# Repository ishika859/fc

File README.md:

# STM32F405 Flight Controller

Custom flight controller board based on the STM32F405RGT6 ARM Cortex-M4 microcontroller.

The board is designed as a compact flight-control platform with an onboard IMU, barometric sensor, four motor outputs, USB-C connectivity, removable storage, multiple serial interfaces and battery monitoring.

This repository contains the KiCad schematic, PCB layout, manufacturing files, bill of materials, firmware starter code and project documentation.

## Why This Project?

The goal of this project was to design a complete flight controller from the schematic level instead of only using an existing development board.

The work included selecting the controller and sensors, designing the power sections, assigning footprints, placing components, routing the PCB, checking the board in KiCad and preparing the manufacturing files.

The project also provides a useful platform for learning how sensor data, motor outputs, communication ports and power monitoring work together in an embedded flight-control system.

## Hardware

| Feature | Description |
|---|---|
| **Microcontroller** | STM32F405RGT6 ARM Cortex-M4, 168 MHz, 1 MB Flash |
| **Inertial sensor** | TDK InvenSense ICM-42688-P 6-axis IMU |
| **Barometer** | Bosch BMP280 pressure sensor |
| **Motor outputs** | Four outputs for M1, M2, M3 and M4 ESC connections |
| **Battery input** | 2S to 6S battery connector with voltage sensing |
| **Current sensing** | Analog current-monitor input |
| **Power regulation** | AP63205WU buck regulator and AP2112K-3.3 LDO |
| **USB connectivity** | USB-C connector with USB ESD protection |
| **Removable storage** | microSD card connector |
| **Serial interfaces** | UART1 receiver, UART3 GPS and I2C, UART4 VTX, UART6 auxiliary port |
| **Debug interface** | 1.27 mm SWD connector |
| **User connections** | LED strip output and buzzer connector |
| **PCB** | Two-layer KiCad PCB layout |

## Main Connections

The ICM-42688-P is connected to the STM32 through SPI. The BMP280 uses the I2C bus shared with the GPS expansion connector.

The four motor nets are connected as follows:

| Motor | MCU pin |
|---|---|
| M1 | PB0 |
| M2 | PB1 |
| M3 | PA3 |
| M4 | PA2 |

The board also includes ADC inputs for battery voltage and current measurement, plus status LEDs and a buzzer driver.

## Project Images

### 3D PCB Design

The board can be inspected in KiCad's 3D Viewer to check component placement, connector access and the overall mechanical layout.

### PCB Layout and Routing

### Circuit Schematic

## Bill of Materials

The component list with purchase links and estimated prices is available in [`bom.csv`](bom.csv).

The current estimated component subtotal is approximately **$31.27 USD** before shipping and taxes. Prices are indicative and can change with supplier stock and order quantity.

Important main parts include:

| Component | Quantity | Description |
|---|---:|---|
| STM32F405RGT6 | 1 | Main flight-controller microcontroller |
| ICM-42688-P | 1 | Accelerometer and gyroscope |
| BMP280 | 1 | Barometric pressure sensor |
| AP63205WU | 1 | Buck regulator |
| AP2112K-3.3 | 1 | 3.3 V linear regulator |
| USBLC6-2SC6 | 1 | USB ESD protection device |
| USB-C receptacle | 1 | USB connection |
| microSD connector | 1 | Flight log storage interface |

## Firmware

The firmware starter is located in [`firmware/`](firmware/).

The initial firmware structure is based on the STM32F405 pin mapping from the schematic and includes the basic peripheral mapping for:

- SPI1 for the ICM-42688-P
- I2C1 for the BMP280
- Four motor output connections
- Battery and current ADC inputs
- UART1, UART3, UART4 and UART6
- USB detect, LEDs and buzzer control

The starter firmware keeps all motor outputs disabled. It is intended for bench testing and peripheral bring-up only. A complete flight firmware still requires sensor initialization, calibration, receiver protocol support, attitude estimation, PID control, motor timing, arming logic and failsafe handling.

Always test firmware with propellers removed until the motor mapping, sensor orientation and failsafe behavior have been verified.

## Repository Structure

```text
hardware/
  flight_controller.kicad_sch
  flight_controller.kicad_pcb

firmware/
  main.c
  README.md

manufacturing/
  gerbers/
  gerbers.zip

documentation/
  project journal and design notes

bom.csv
README.md
```

## Design Verification

The current PCB has been checked in KiCad and the present board revision reports no remaining DRC warnings or errors.

The schematic and PCB should still be reviewed against the final assembled components before ordering. Particular attention should be given to the USB-C shell pads, connector mounting pads, regulator layout, sensor orientation and the motor-output order.

## Manufacturing

The `manufacturing/gerbers/` folder contains the exported Gerber and drill files needed to order the PCB.

The manufacturing package includes:

- Front and back copper
- Front and back solder mask
- Front and back silkscreen
- Paste layers where required
- Edge cuts board outline
- Plated and non-plated drill files
- Gerber job file

Before ordering, upload the Gerber archive to the chosen PCB manufacturer and confirm that the board outline, layer count, drill files and solder-mask openings are detected correctly.

## Project Status

The hardware design, schematic, PCB layout, BOM and manufacturing outputs are complete for the current revision.

The next stage is hardware bring-up. This includes checking the power rails, programming through SWD, confirming USB communication, reading the IMU and barometer, testing the ADC inputs and validating each motor output independently.

## License

Add the project license here before publishing the repository.

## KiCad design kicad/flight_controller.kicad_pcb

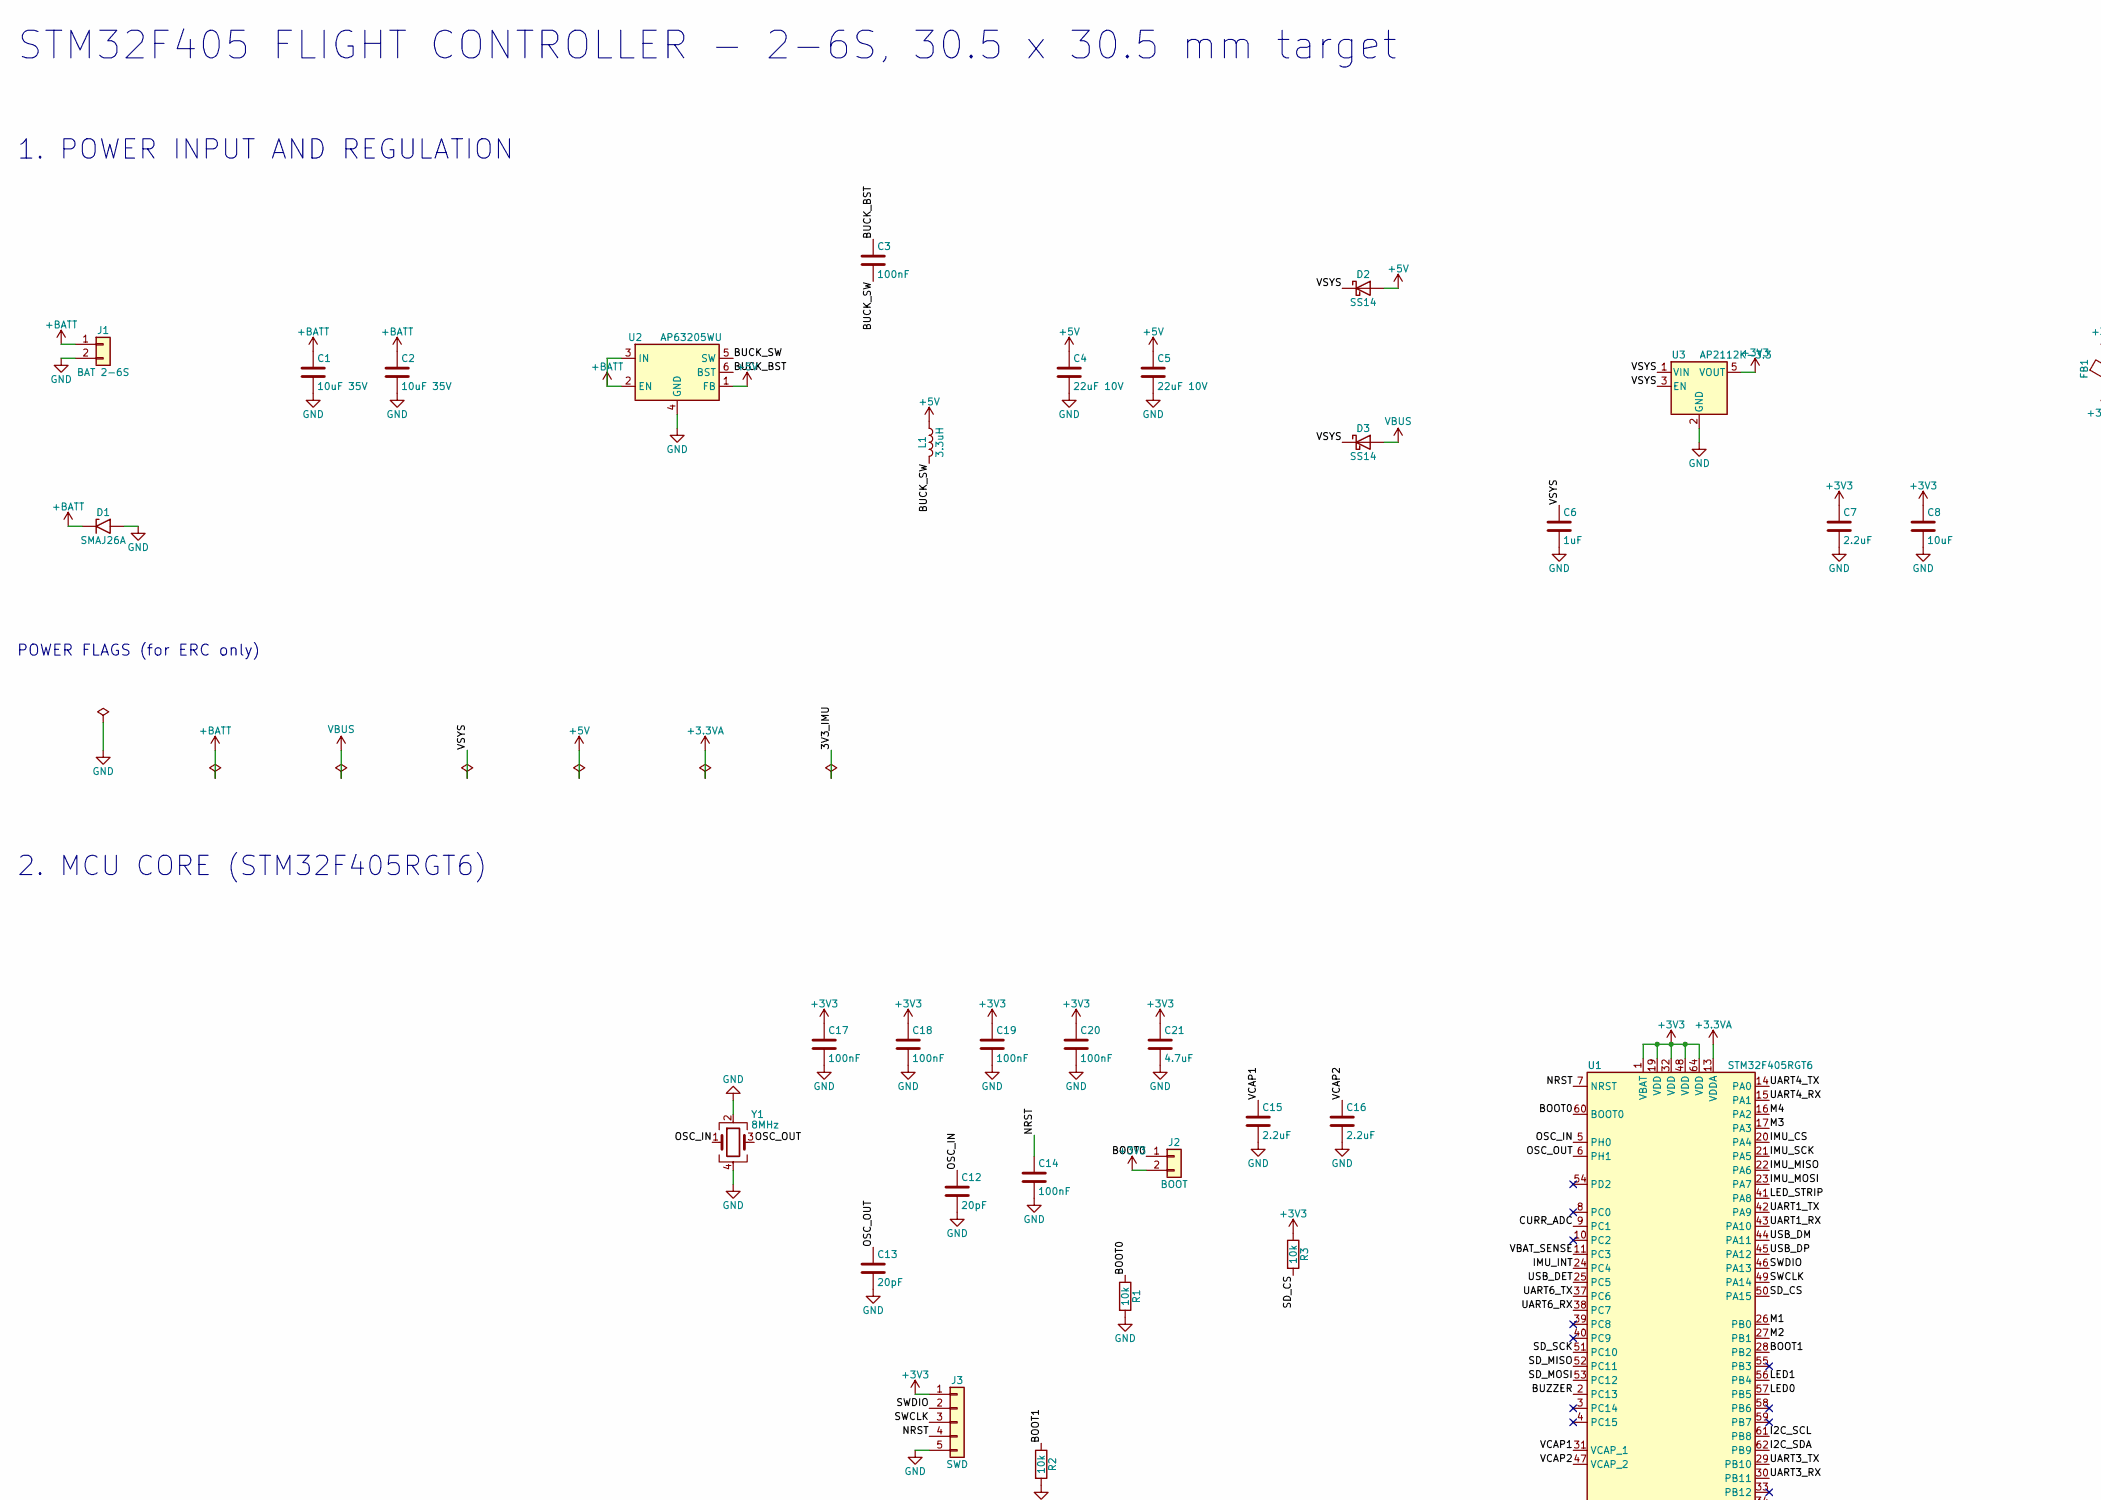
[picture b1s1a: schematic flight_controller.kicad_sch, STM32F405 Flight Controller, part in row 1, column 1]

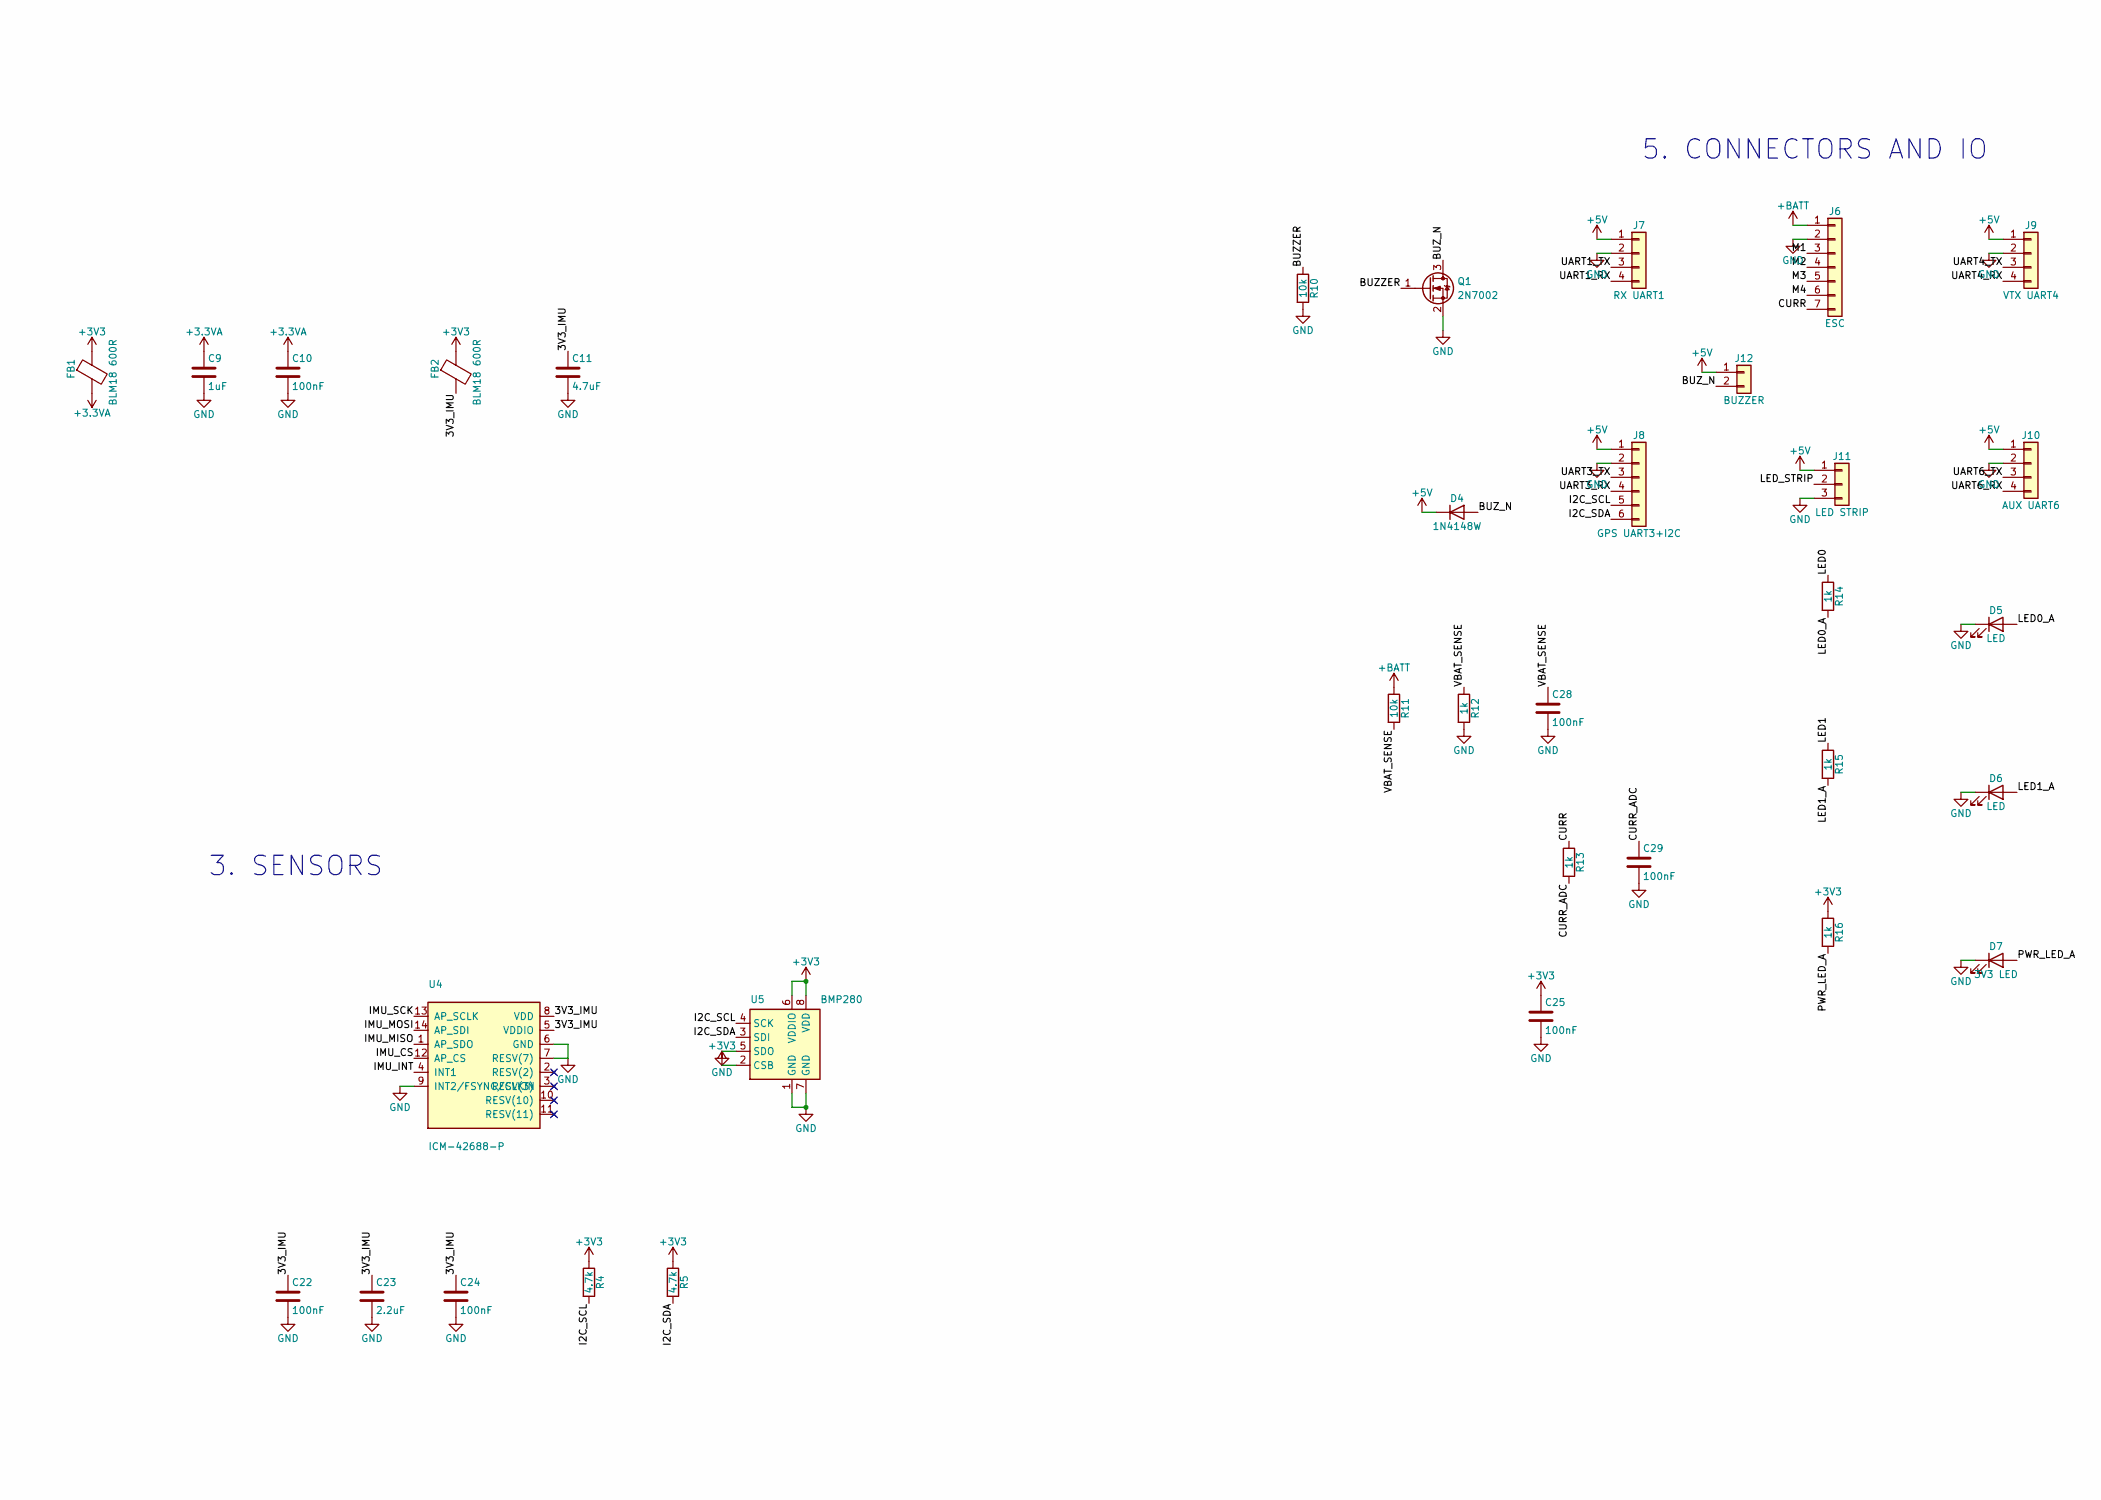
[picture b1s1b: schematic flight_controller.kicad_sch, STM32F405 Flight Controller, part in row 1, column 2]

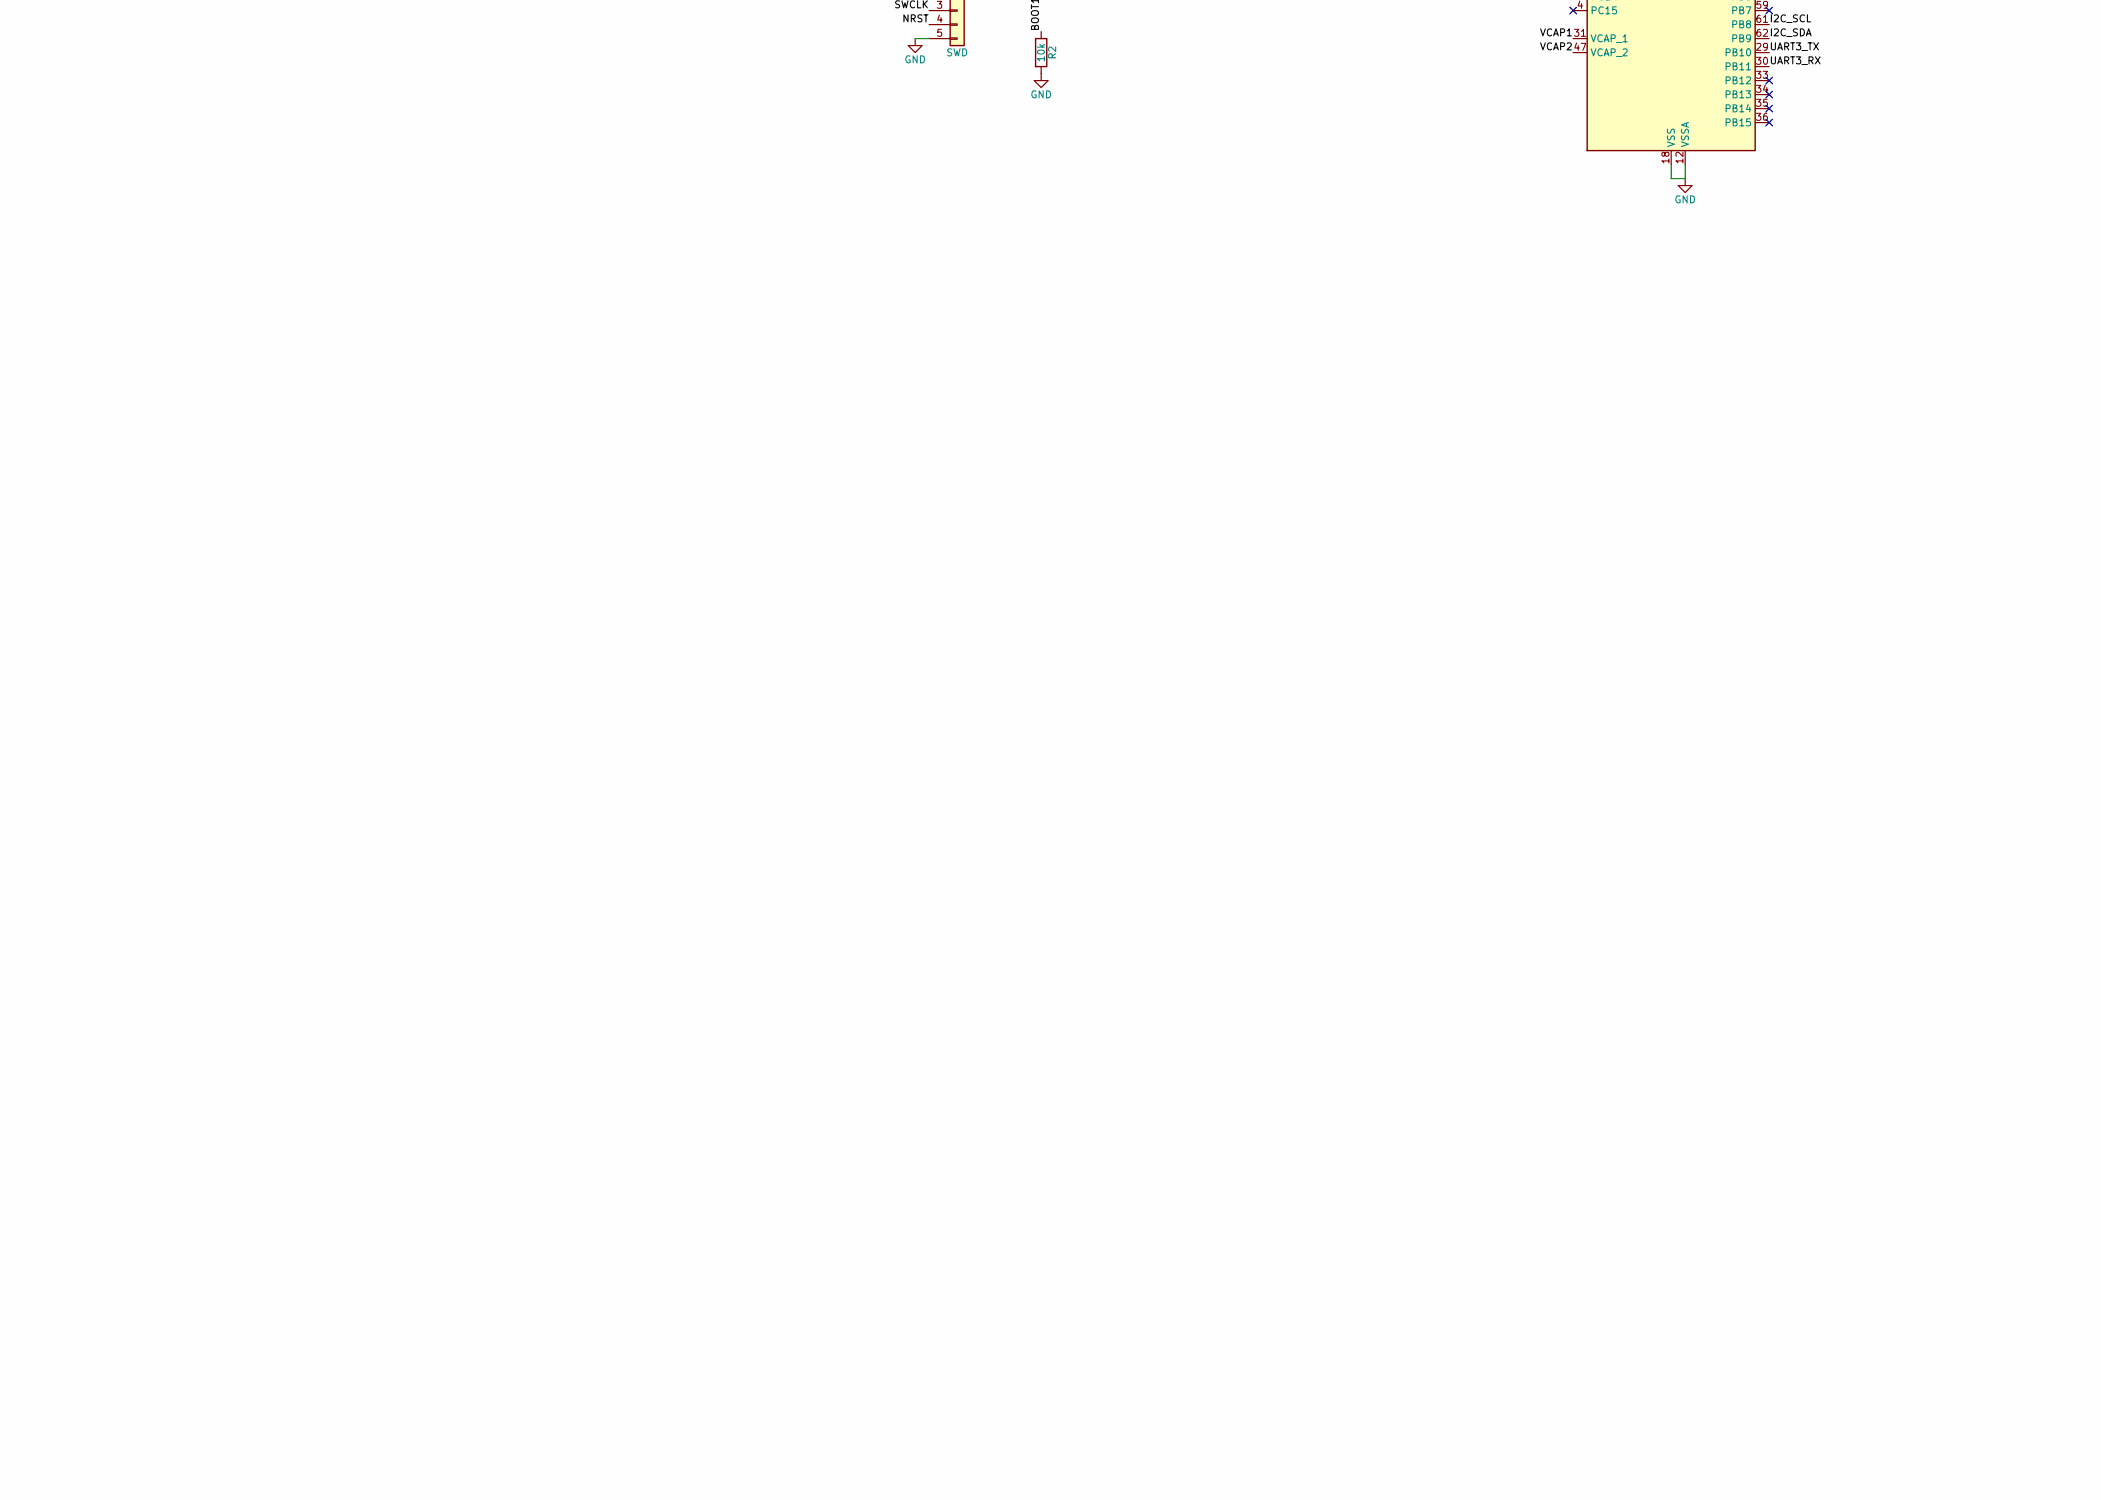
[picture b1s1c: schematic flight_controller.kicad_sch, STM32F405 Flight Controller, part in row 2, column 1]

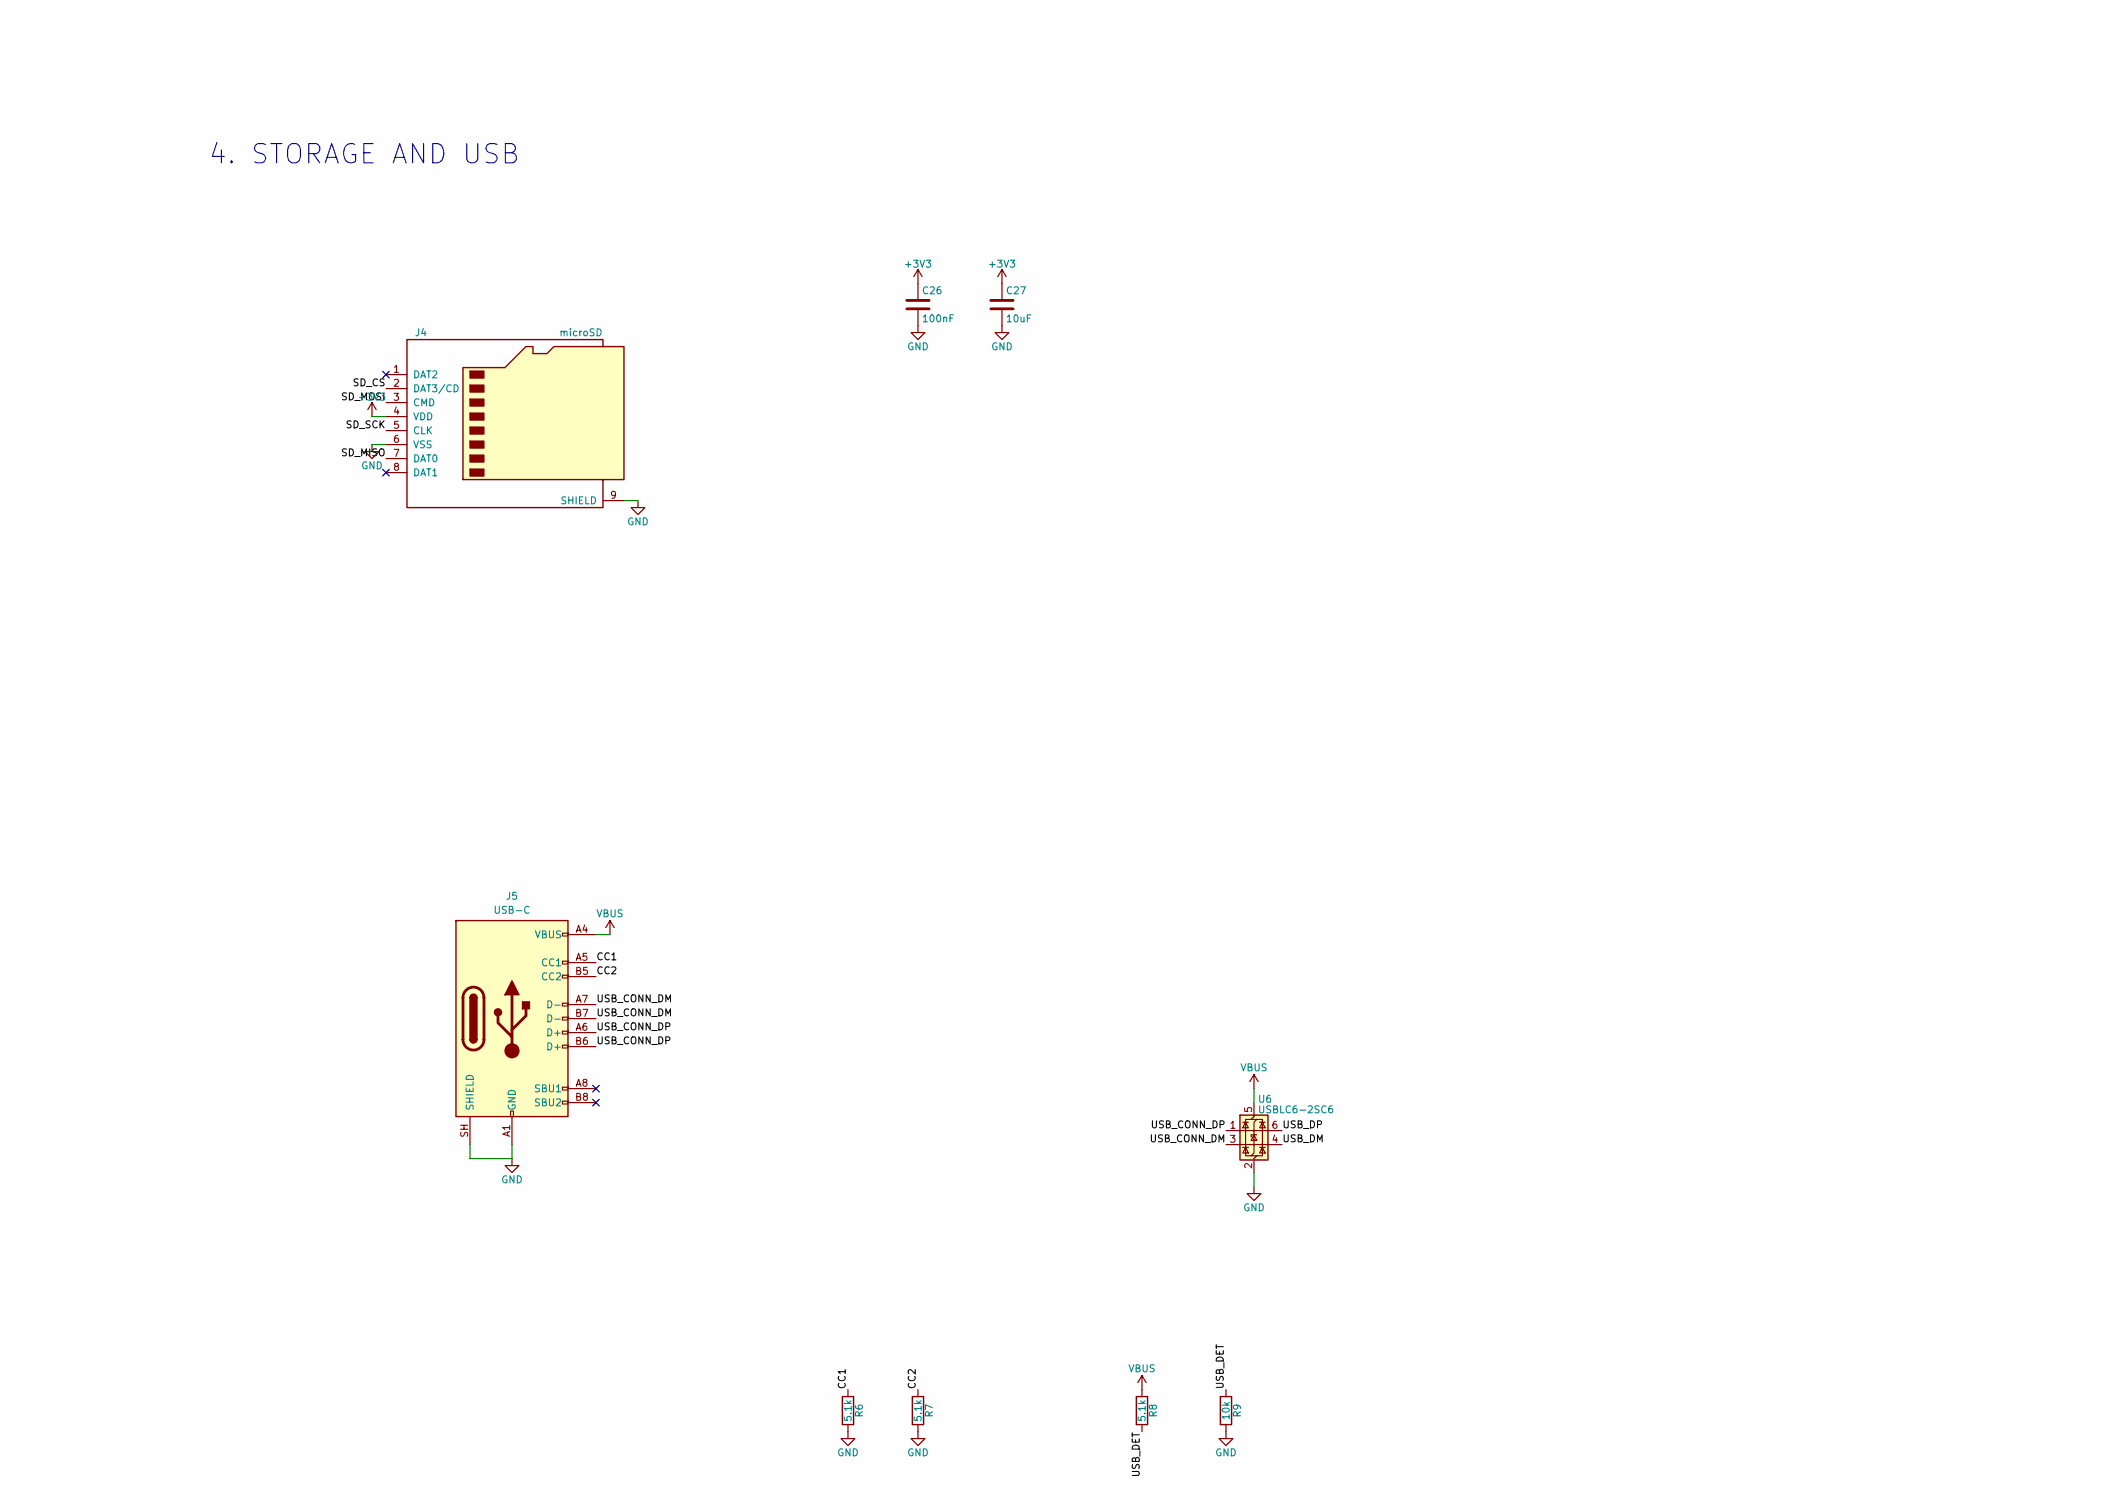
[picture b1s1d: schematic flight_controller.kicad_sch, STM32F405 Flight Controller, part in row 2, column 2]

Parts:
C1, C2: 10uF 35V; C_1206_3216Metric
C3, C10, C14, C17, C18, C19, C20, C22, C24, C25, C26, C28, C29: 100nF; C_0402_1005Metric
C4, C5: 22uF 10V; C_0805_2012Metric
C6, C9: 1uF; C_0402_1005Metric
C7, C15, C16, C23: 2.2uF; C_0402_1005Metric
C8, C27: 10uF; C_0805_2012Metric
C11, C21: 4.7uF; C_0805_2012Metric
C12, C13: 20pF; C_0402_1005Metric
D1: SMAJ26A; D_SMA
D2, D3: SS14; D_SMA
D4: 1N4148W; D_SOD-123
D5, D6: LED; LED_0603_1608Metric
D7: 3V3 LED; LED_0603_1608Metric
FB1, FB2: BLM18 600R; L_0603_1608Metric
J1: BAT 2-6S; PinHeader_1x02_P2.54mm_Vertical
J2: BOOT; PinHeader_1x02_P1.27mm_Vertical
J3: SWD; PinHeader_1x05_P1.27mm_Vertical
J4: microSD; microSD_HC_Hirose_DM3AT-SF-PEJM5
J5: USB-C; USB_C_Receptacle_HRO_TYPE-C-31-M-12
J6: ESC; PinHeader_1x07_P1.00mm_Vertical
J7: RX UART1; JST_SH_SM04B-SRSS-TB_1x04-1MP_P1.00mm_Horizontal
J8: GPS UART3+I2C; JST_SH_SM06B-SRSS-TB_1x06-1MP_P1.00mm_Horizontal
J9: VTX UART4; JST_SH_SM04B-SRSS-TB_1x04-1MP_P1.00mm_Horizontal
J10: AUX UART6; JST_SH_SM04B-SRSS-TB_1x04-1MP_P1.00mm_Horizontal
J11: LED STRIP; JST_SH_SM03B-SRSS-TB_1x03-1MP_P1.00mm_Horizontal
J12: BUZZER; PinHeader_1x02_P1.27mm_Vertical
L1: 3.3uH; L_Taiyo-Yuden_NR-50xx
Q1: 2N7002; SOT-23
R1, R2, R3, R9, R10, R11: 10k; R_0402_1005Metric
R4, R5: 4.7k; R_0402_1005Metric
R6, R7, R8: 5.1k; R_0402_1005Metric
R12, R13, R14, R15, R16: 1k; R_0402_1005Metric
U1: STM32F405RGT6; LQFP-64_10x10mm_P0.5mm
U2: AP63205WU; TSOT-23-6
U3: AP2112K-3.3; SOT-23-5
U4: ICM-42688-P; LGA-14_3x2.5mm_P0.5mm_LayoutBorder3x4y
U5: BMP280; Bosch_LGA-8_2x2.5mm_P0.65mm_ClockwisePinNumbering
U6: USBLC6-2SC6; SOT-23-6
Y1: 8MHz; Crystal_SMD_3225-4Pin_3.2x2.5mm

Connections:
+3.3VA: C9.1, C10.1, FB1.2, U1.13 (VDDA)
+3V3: C7.1, C8.1, C17.1, C18.1, C19.1, C20.1, C21.1, C25.1, C26.1, C27.1, FB1.1, FB2.1, J2.2, J3.1, J4.4 (VDD), R3.1, R4.1, R5.1, R16.1, U1.1 (VBAT), U1.19 (VDD), U1.32 (VDD), U1.48 (VDD), U1.64 (VDD), U3.5 (VOUT), U5.2 (CSB), U5.6 (VDDIO), U5.8 (VDD)
+5V: C4.1, C5.1, D2.2 (A), D4.1 (K), J7.1, J8.1, J9.1, J10.1, J11.1, J12.1, L1.1, U2.1 (FB)
+BATT: C1.1, C2.1, D1.1 (A1), J1.1, J6.1, R11.1, U2.2 (EN), U2.3 (IN)
/3V3_IMU: C11.1, C22.1, C23.1, C24.1, FB2.2, U4.5 (VDDIO), U4.8 (VDD)
/BOOT0: J2.1, R1.1, U1.60 (BOOT0)
/BOOT1: R2.1, U1.28 (PB2)
/BUCK_BST: C3.1, U2.6 (BST)
/BUCK_SW: C3.2, L1.2, U2.5 (SW)
/BUZZER: Q1.1 (G), R10.1, U1.2 (PC13)
/BUZ_N: D4.2 (A), J12.2, Q1.3 (D)
/CC1: J5.A5 (CC1), R6.1
/CC2: J5.B5 (CC2), R7.1
/CURR: J6.7, R13.1
/CURR_ADC: C29.1, R13.2, U1.9 (PC1)
/I2C_SCL: J8.5, R4.2, U1.61 (PB8), U5.4 (SCK)
/I2C_SDA: J8.6, R5.2, U1.62 (PB9), U5.3 (SDI)
/IMU_CS: U1.20 (PA4), U4.12 (AP_CS)
/IMU_INT: U1.24 (PC4), U4.4 (INT1)
/IMU_MISO: U1.22 (PA6), U4.1 (AP_SDO)
/IMU_MOSI: U1.23 (PA7), U4.14 (AP_SDI)
/IMU_SCK: U1.21 (PA5), U4.13 (AP_SCLK)
/LED0: R14.1, U1.57 (PB5)
/LED0_A: D5.2 (A), R14.2
/LED1: R15.1, U1.56 (PB4)
/LED1_A: D6.2 (A), R15.2
/LED_STRIP: J11.2, U1.41 (PA8)
/M1: J6.3, U1.26 (PB0)
/M2: J6.4, U1.27 (PB1)
/M3: J6.5, U1.17 (PA3)
/M4: J6.6, U1.16 (PA2)
/NRST: C14.1, J3.4, U1.7 (NRST)
/OSC_IN: C12.1, U1.5 (PH0), Y1.1
/OSC_OUT: C13.1, U1.6 (PH1), Y1.3
/PWR_LED_A: D7.2 (A), R16.2
/SD_CS: J4.2 (DAT3/CD), R3.2, U1.50 (PA15)
/SD_MISO: J4.7 (DAT0), U1.52 (PC11)
/SD_MOSI: J4.3 (CMD), U1.53 (PC12)
/SD_SCK: J4.5 (CLK), U1.51 (PC10)
/SWCLK: J3.3, U1.49 (PA14)
/SWDIO: J3.2, U1.46 (PA13)
/UART1_RX: J7.4, U1.43 (PA10)
/UART1_TX: J7.3, U1.42 (PA9)
/UART3_RX: J8.4, U1.30 (PB11)
/UART3_TX: J8.3, U1.29 (PB10)
/UART4_RX: J9.4, U1.15 (PA1)
/UART4_TX: J9.3, U1.14 (PA0)
/UART6_RX: J10.4, U1.38 (PC7)
/UART6_TX: J10.3, U1.37 (PC6)
/USB_CONN_DM: J5.A7 (D-), J5.B7 (D-), U6.3 (I/O2)
/USB_CONN_DP: J5.A6 (D+), J5.B6 (D+), U6.1 (I/O1)
/USB_DET: R8.2, R9.1, U1.25 (PC5)
/USB_DM: U1.44 (PA11), U6.4 (I/O2)
/USB_DP: U1.45 (PA12), U6.6 (I/O1)
/VBAT_SENSE: C28.1, R11.2, R12.1, U1.11 (PC3)
/VCAP1: C15.1, U1.31 (VCAP_1)
/VCAP2: C16.1, U1.47 (VCAP_2)
/VSYS: C6.1, D2.1 (K), D3.1 (K), U3.1 (VIN), U3.3 (EN)
GND: C1.2, C2.2, C4.2, C5.2, C6.2, C7.2, C8.2, C9.2, C10.2, C11.2, C12.2, C13.2, C14.2, C15.2, C16.2, C17.2, C18.2, C19.2, C20.2, C21.2, C22.2, C23.2, C24.2, C25.2, C26.2, C27.2, C28.2, C29.2, D1.2 (A2), D5.1 (K), D6.1 (K), D7.1 (K), J1.2, J3.5, J4.6 (VSS), J4.9 (SHIELD), J5.A1 (GND), J5.A12 (GND), J5.B1 (GND), J5.B12 (GND), J5.SH (SHIELD), J6.2, J7.2, J8.2, J9.2, J10.2, J11.3, Q1.2 (S), R1.2, R2.2, R6.2, R7.2, R9.2, R10.2, R12.2, U1.12 (VSSA), U1.18 (VSS), U1.63 (VSS), U2.4 (GND), U3.2 (GND), U4.6 (GND), U4.7 (RESV(7)), U4.9 (INT2/FSYNC/CLKIN), U5.1 (GND), U5.5 (SDO), U5.7 (GND), U6.2 (GND), Y1.2, Y1.4
VBUS: D3.2 (A), J5.A4 (VBUS), J5.A9 (VBUS), J5.B4 (VBUS), J5.B9 (VBUS), R8.1, U6.5 (VBUS)

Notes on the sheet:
1. POWER INPUT AND REGULATION
5. CONNECTORS AND IO
4. STORAGE AND USB
3. SENSORS
2. MCU CORE (STM32F405RGT6)
POWER FLAGS (for ERC only)
STM32F405 FLIGHT CONTROLLER - 2-6S, 30.5 x 30.5 mm target

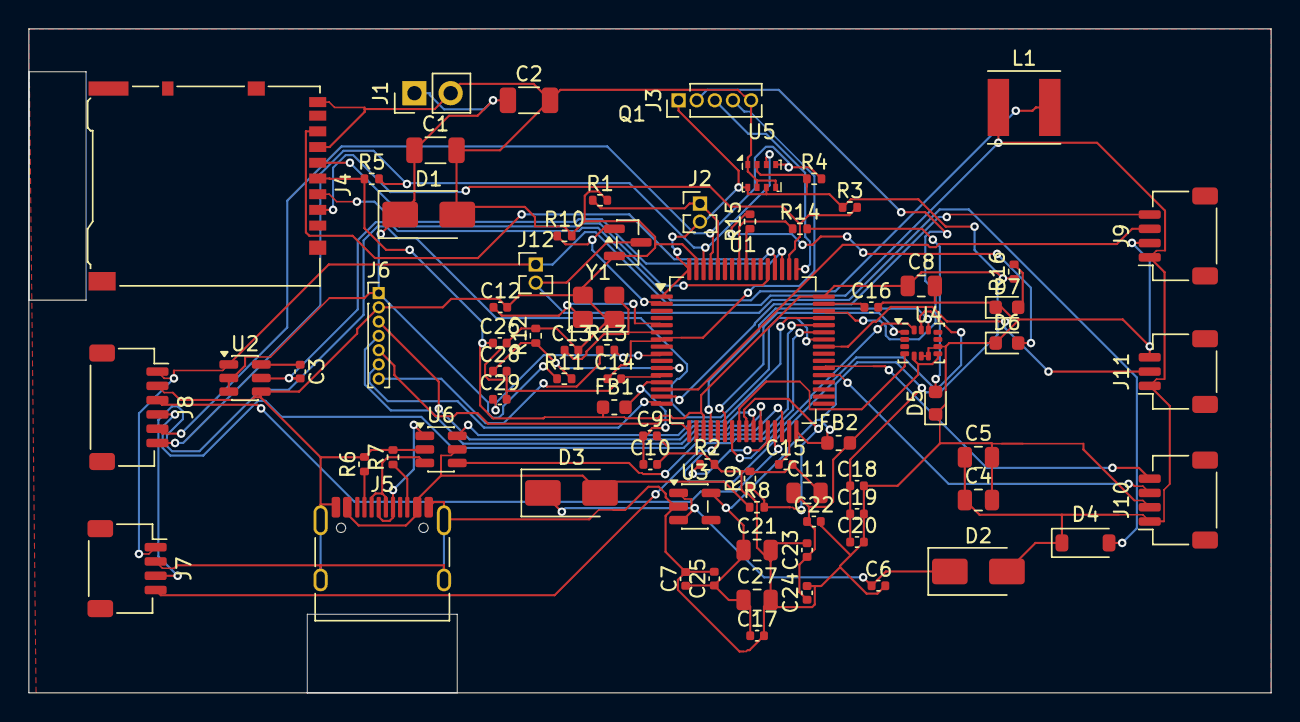
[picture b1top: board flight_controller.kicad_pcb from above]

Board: 2 copper layers, 87.0 x 46.5 mm, 75 parts (0 on the bottom side), 60 nets.

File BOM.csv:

"Id";"Designator";"Footprint";"Quantity";"Designation";"Supplier and ref";
1;"C1, C2";"C_1206_3216Metric";2;"10uF 35V";;;
2;"C3, C10, C14, C17, C18, C19, C20, C22, C24, C25, C26, C28, C29";"C_0402_1005Metric";13;"100nF";;;
3;"C4, C5";"C_0805_2012Metric";2;"22uF 10V";;;
4;"C6, C9";"C_0402_1005Metric";2;"1uF";;;
5;"C7, C15, C16, C23";"C_0402_1005Metric";4;"2.2uF";;;
6;"C8, C27";"C_0805_2012Metric";2;"10uF";;;
7;"C11, C21";"C_0805_2012Metric";2;"4.7uF";;;
8;"C12, C13";"C_0402_1005Metric";2;"20pF";;;
9;"D1";"D_SMA";1;"SMAJ26A";;;
10;"D2, D3";"D_SMA";2;"SS14";;;
11;"D4";"D_SOD-123";1;"1N4148W";;;
12;"D5, D6";"LED_0603_1608Metric";2;"LED";;;
13;"D7";"LED_0603_1608Metric";1;"3V3 LED";;;
14;"FB1, FB2";"L_0603_1608Metric";2;"BLM18 600R";;;
15;"J1";"PinHeader_1x02_P2.54mm_Vertical";1;"BAT 2-6S";;;
16;"J2";"PinHeader_1x02_P1.27mm_Vertical";1;"BOOT";;;
17;"J3";"PinHeader_1x05_P1.27mm_Vertical";1;"SWD";;;
18;"J4";"microSD_HC_Hirose_DM3AT-SF-PEJM5";1;"microSD";;;
19;"J5";"USB_C_Receptacle_HRO_TYPE-C-31-M-12";1;"USB-C";;;
20;"J6";"PinHeader_1x07_P1.00mm_Vertical";1;"ESC";;;
21;"J7";"JST_SH_SM04B-SRSS-TB_1x04-1MP_P1.00mm_Horizontal";1;"RX UART1";;;
22;"J8";"JST_SH_SM06B-SRSS-TB_1x06-1MP_P1.00mm_Horizontal";1;"GPS UART3+I2C";;;
23;"J9";"JST_SH_SM04B-SRSS-TB_1x04-1MP_P1.00mm_Horizontal";1;"VTX UART4";;;
24;"J10";"JST_SH_SM04B-SRSS-TB_1x04-1MP_P1.00mm_Horizontal";1;"AUX UART6";;;
25;"J11";"JST_SH_SM03B-SRSS-TB_1x03-1MP_P1.00mm_Horizontal";1;"LED STRIP";;;
26;"J12";"PinHeader_1x02_P1.27mm_Vertical";1;"BUZZER";;;
27;"L1";"L_Taiyo-Yuden_NR-50xx";1;"3.3uH";;;
28;"Q1";"SOT-23";1;"2N7002";;;
29;"R1, R2, R3, R9, R10, R11";"R_0402_1005Metric";6;"10k";;;
30;"R4, R5";"R_0402_1005Metric";2;"4.7k";;;
31;"R6, R7, R8";"R_0402_1005Metric";3;"5.1k";;;
32;"R12, R13, R14, R15, R16";"R_0402_1005Metric";5;"1k";;;
33;"U1";"LQFP-64_10x10mm_P0.5mm";1;"STM32F405RGT6";;;
34;"U2";"TSOT-23-6";1;"AP63205WU";;;
35;"U3";"SOT-23-5";1;"AP2112K-3.3";;;
36;"U4";"LGA-14_3x2.5mm_P0.5mm_LayoutBorder3x4y";1;"ICM-42688-P";;;
37;"U5";"Bosch_LGA-8_2x2.5mm_P0.65mm_ClockwisePinNumbering";1;"BMP280";;;
38;"U6";"SOT-23-6";1;"USBLC6-2SC6";;;
39;"Y1";"Crystal_SMD_3225-4Pin_3.2x2.5mm";1;"8MHz";;;

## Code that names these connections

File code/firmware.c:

#include "main.h"
#include <stdint.h>

extern SPI_HandleTypeDef hspi1;
extern I2C_HandleTypeDef hi2c1;
extern ADC_HandleTypeDef hadc1;
extern TIM_HandleTypeDef htim3;

#define IMU_CS_PORT GPIOA
#define IMU_CS_PIN  GPIO_PIN_4

#define LED0_PORT GPIOB
#define LED0_PIN  GPIO_PIN_5
#define LED1_PORT GPIOB
#define LED1_PIN  GPIO_PIN_4
#define BUZZER_PORT GPIOC
#define BUZZER_PIN  GPIO_PIN_13

#define M1_PORT GPIOB
#define M1_PIN  GPIO_PIN_0
#define M2_PORT GPIOB
#define M2_PIN  GPIO_PIN_1
#define M3_PORT GPIOA
#define M3_PIN  GPIO_PIN_3
#define M4_PORT GPIOA
#define M4_PIN  GPIO_PIN_2

static volatile uint8_t armed = 0;

static void motors_all_off(void)
{
    HAL_GPIO_WritePin(M1_PORT, M1_PIN, GPIO_PIN_RESET);
    HAL_GPIO_WritePin(M2_PORT, M2_PIN, GPIO_PIN_RESET);
    HAL_GPIO_WritePin(M3_PORT, M3_PIN, GPIO_PIN_RESET);
    HAL_GPIO_WritePin(M4_PORT, M4_PIN, GPIO_PIN_RESET);
    armed = 0;
}

static void status_led_task(void)
{
    static uint32_t last_tick = 0;
    if ((HAL_GetTick() - last_tick) >= 500U) {
        last_tick = HAL_GetTick();
        HAL_GPIO_TogglePin(LED0_PORT, LED0_PIN);
    }
}

static uint16_t read_adc_channel(void)
{
    HAL_ADC_Start(&hadc1);
    HAL_ADC_PollForConversion(&hadc1, 10U);
    uint16_t value = (uint16_t)HAL_ADC_GetValue(&hadc1);
    HAL_ADC_Stop(&hadc1);
    return value;
}

int main(void)
{
    HAL_Init();
    SystemClock_Config();
    MX_GPIO_Init();
    MX_DMA_Init();
    MX_ADC1_Init();
    MX_I2C1_Init();
    MX_SPI1_Init();
    MX_TIM3_Init();

    HAL_GPIO_WritePin(IMU_CS_PORT, IMU_CS_PIN, GPIO_PIN_SET);
    HAL_GPIO_WritePin(BUZZER_PORT, BUZZER_PIN, GPIO_PIN_RESET);
    motors_all_off();

    for (;;) {
        (void)read_adc_channel();
        motors_all_off();
        status_led_task();
        HAL_Delay(2U);
    }
}
